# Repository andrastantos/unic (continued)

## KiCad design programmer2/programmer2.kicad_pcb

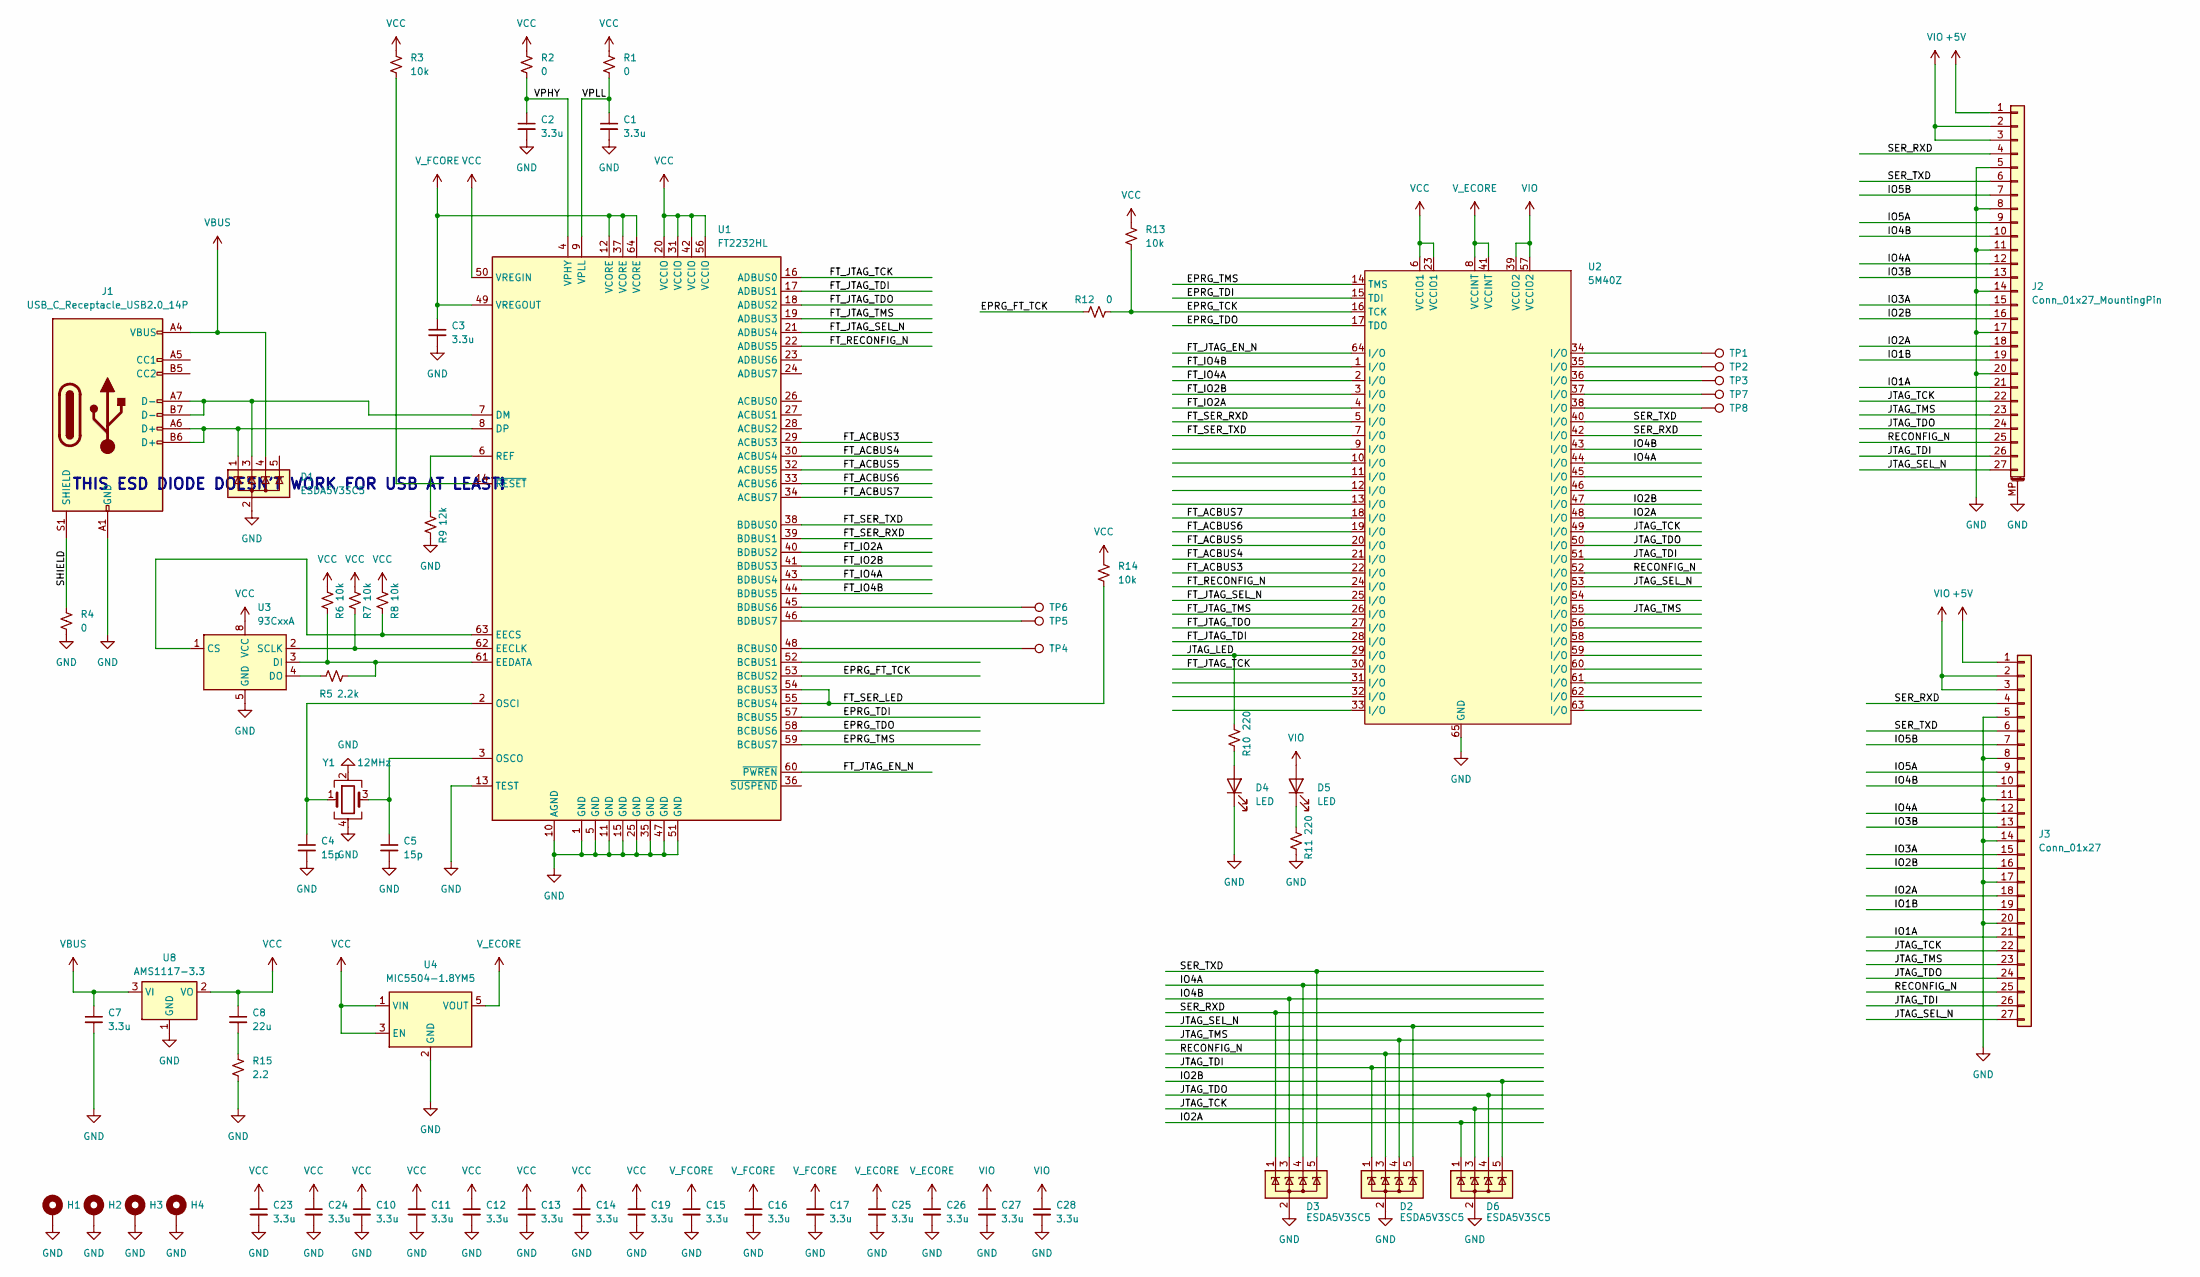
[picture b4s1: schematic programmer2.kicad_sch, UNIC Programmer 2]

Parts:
C1, C2, C3, C7, C10, C11, C12, C13, C14, C15, C16, C17, C19, C23, C24, C25, C26, C27, C28: 3.3u; C_0603_1608Metric_Pad1.08x0.95mm_HandSolder
C4, C5: 15p; C_0603_1608Metric_Pad1.08x0.95mm_HandSolder
C8: 22u; C_0805_2012Metric_Pad1.18x1.45mm_HandSolder
D1, D2, D3, D6: ESDA5V3SC5; SOT-23-5
D4, D5: LED; LED_0603_1608Metric_Pad1.05x0.95mm_HandSolder
H1, H2, H3, H4: MountingHole; MountingHole_3.2mm_M3_DIN965_Pad
J1: USB_C_Receptacle_USB2.0_14P; USB_C_Receptacle_HRO_TYPE-C-31-M-12; mpn 44116B01231
J2: Conn_01x27_MountingPin; Molex_502598-2793_2Rows-23P~0.60mm_Horizontal; mpn 502598-2793
J3: Conn_01x27; PinHeader_2x14_P2.54mm_Vertical
R1, R2, R4, R12: 0; R_0603_1608Metric_Pad0.98x0.95mm_HandSolder
R3, R6, R7, R8, R13, R14: 10k; R_0603_1608Metric_Pad0.98x0.95mm_HandSolder
R5: 2.2k; R_0603_1608Metric_Pad0.98x0.95mm_HandSolder
R9: 12k; R_0603_1608Metric_Pad0.98x0.95mm_HandSolder
R10, R11: 220; R_0603_1608Metric_Pad0.98x0.95mm_HandSolder
R15: 2.2; R_0603_1608Metric_Pad0.98x0.95mm_HandSolder
TP1, TP2, TP3, TP4, TP5, TP6, TP7, TP8: TestPoint; TestPoint_THTPad_1.0x1.0mm_Drill0.5mm
U1: FT2232HL; LQFP-64_10x10mm_P0.5mm
U2: 5M40Z; TQFP-64-1EP_10x10mm_P0.5mm_EP8x8mm
U3: 93CxxA; SO-8_3.9x4.9mm_P1.27mm
U4: MIC5504-1.8YM5; SOT-23-5
U8: AMS1117-3.3; SOT-223-3_TabPin2
Y1: 12MHz; Oscillator_SMD_Abracon_ASE-4Pin_3.2x2.5mm; mpn RH100-13.560-10-1020-EXT-TR

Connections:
+5V: J2.1, J3.1
/EPRG_FT_TCK: R12.1, U1.53 (BCBUS2)
/EPRG_TCK: R12.2, R13.2, U2.16 (TCK)
/EPRG_TDI: U1.57 (BCBUS5), U2.15 (TDI)
/EPRG_TDO: U1.58 (BCBUS6), U2.17 (TDO)
/EPRG_TMS: U1.59 (BCBUS7), U2.14 (TMS)
/FT_ACBUS3: U1.29 (ACBUS3), U2.22 (I/O)
/FT_ACBUS4: U1.30 (ACBUS4), U2.21 (I/O)
/FT_ACBUS5: U1.32 (ACBUS5), U2.20 (I/O)
/FT_ACBUS6: U1.33 (ACBUS6), U2.19 (I/O)
/FT_ACBUS7: U1.34 (ACBUS7), U2.18 (I/O)
/FT_IO2A: U1.40 (BDBUS2), U2.4 (I/O)
/FT_IO2B: U1.41 (BDBUS3), U2.3 (I/O)
/FT_IO4A: U1.43 (BDBUS4), U2.2 (I/O)
/FT_IO4B: U1.44 (BDBUS5), U2.1 (I/O)
/FT_JTAG_EN_N: U1.60 (~PWREN), U2.64 (I/O)
/FT_JTAG_SEL_N: U1.21 (ADBUS4), U2.25 (I/O)
/FT_JTAG_TCK: U1.16 (ADBUS0), U2.30 (I/O)
/FT_JTAG_TDI: U1.17 (ADBUS1), U2.28 (I/O)
/FT_JTAG_TDO: U1.18 (ADBUS2), U2.27 (I/O)
/FT_JTAG_TMS: U1.19 (ADBUS3), U2.26 (I/O)
/FT_RECONFIG_N: U1.22 (ADBUS5), U2.24 (I/O)
/FT_SER_LED: R14.2, U1.54 (BCBUS3), U1.55 (BCBUS4)
/FT_SER_RXD: U1.39 (BDBUS1), U2.5 (I/O)
/FT_SER_TXD: U1.38 (BDBUS0), U2.7 (I/O)
/IO1A: J2.21, J3.21
/IO1B: J2.19, J3.19
/IO2A: D6.1 (K), J2.18, J3.18, U2.48 (I/O)
/IO2B: D6.5 (K), J2.16, J3.16, U2.47 (I/O)
/IO3A: J2.15, J3.15
/IO3B: J2.13, J3.13
/IO4A: D3.4 (K), J2.12, J3.12, U2.44 (I/O)
/IO4B: D3.3 (K), J2.10, J3.10, U2.43 (I/O)
/IO5A: J2.9, J3.9
/IO5B: J2.7, J3.7
/JTAG_LED: R10.1, U2.29 (I/O)
/JTAG_SEL_N: D2.5 (K), J2.27, J3.27, U2.53 (I/O)
/JTAG_TCK: D6.3 (K), J2.22, J3.22, U2.49 (I/O)
/JTAG_TDI: D2.1 (K), J2.26, J3.26, U2.51 (I/O)
/JTAG_TDO: D6.4 (K), J2.24, J3.24, U2.50 (I/O)
/JTAG_TMS: D2.4 (K), J2.23, J3.23, U2.55 (I/O)
/RECONFIG_N: D2.3 (K), J2.25, J3.25, U2.52 (I/O)
/SER_RXD: D3.1 (K), J2.4, J3.4, U2.42 (I/O)
/SER_TXD: D3.5 (K), J2.6, J3.6, U2.40 (I/O)
/SHIELD: J1.S1 (SHIELD), R4.1
/VPHY: C2.1, R2.2, U1.4 (VPHY)
/VPLL: C1.1, R1.2, U1.9 (VPLL)
GND: C1.2, C2.2, C3.2, C4.2, C5.2, C7.2, C10.2, C11.2, C12.2, C13.2, C14.2, C15.2, C16.2, C17.2, C19.2, C23.2, C24.2, C25.2, C26.2, C27.2, C28.2, D1.2 (A), D2.2 (A), D3.2 (A), D4.1 (K), D6.2 (A), H1.1, H2.1, H3.1, H4.1, J1.A1 (GND), J1.A12 (GND), J1.B1 (GND), J1.B12 (GND), J2.5, J2.8, J2.11, J2.14, J2.17, J2.20, J2.MP (MountPin), J3.5, J3.8, J3.11, J3.14, J3.17, J3.20, R4.2, R9.2, R11.2, R15.2, U1.1 (GND), U1.5 (GND), U1.10 (AGND), U1.11 (GND), U1.13 (TEST), U1.15 (GND), U1.25 (GND), U1.35 (GND), U1.47 (GND), U1.51 (GND), U2.65 (GND), U3.5 (GND), U4.2 (GND), U8.1 (GND), Y1.2, Y1.4
unnamed: C8.2, R15.1
unnamed: D4.2 (A), R10.2
unnamed: D5.1 (K), R11.1
unnamed: TP1.1, U2.34 (I/O)
unnamed: TP2.1, U2.35 (I/O)
unnamed: TP3.1, U2.36 (I/O)
unnamed: TP7.1, U2.37 (I/O)
unnamed: TP8.1, U2.38 (I/O)
unnamed: TP4.1, U1.48 (BCBUS0)
unnamed: TP6.1, U1.45 (BDBUS6)
unnamed: TP5.1, U1.46 (BDBUS7)
unnamed: D1.3 (K), J1.A7 (D-), J1.B7 (D-), U1.7 (DM)
unnamed: D1.1 (K), J1.A6 (D+), J1.B6 (D+), U1.8 (DP)
unnamed: R7.2, U1.62 (EECLK), U3.2 (SCLK)
unnamed: R8.2, U1.63 (EECS), U3.1 (CS)
unnamed: R5.2, R6.2, U1.61 (EEDATA), U3.3 (DI)
unnamed: C4.1, U1.2 (OSCI), Y1.1
unnamed: C5.1, U1.3 (OSCO), Y1.3
unnamed: R9.1, U1.6 (REF)
unnamed: R3.2, U1.14 (~RESET)
unnamed: R5.1, U3.4 (DO)
VBUS: C7.1, D1.4 (K), J1.A4 (VBUS), J1.A9 (VBUS), J1.B4 (VBUS), J1.B9 (VBUS), U8.3 (VI)
VCC: C8.1, C10.1, C11.1, C12.1, C13.1, C14.1, C19.1, C23.1, C24.1, R1.1, R2.1, R3.1, R6.1, R7.1, R8.1, R13.1, R14.1, U1.20 (VCCIO), U1.31 (VCCIO), U1.42 (VCCIO), U1.50 (VREGIN), U1.56 (VCCIO), U2.6 (VCCIO1), U2.23 (VCCIO1), U3.8 (VCC), U4.1 (VIN), U4.3 (EN), U8.2 (VO)
VIO: C27.1, C28.1, D5.2 (A), J2.2, J2.3, J3.2, J3.3, U2.39 (VCCIO2), U2.57 (VCCIO2)
V_ECORE: C25.1, C26.1, U2.8 (VCCINT), U2.41 (VCCINT), U4.5 (VOUT)
V_FCORE: C3.1, C15.1, C16.1, C17.1, U1.12 (VCORE), U1.37 (VCORE), U1.49 (VREGOUT), U1.64 (VCORE)

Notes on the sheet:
THIS ESD DIODE DOESN'T WORK FOR USB AT LEAST!

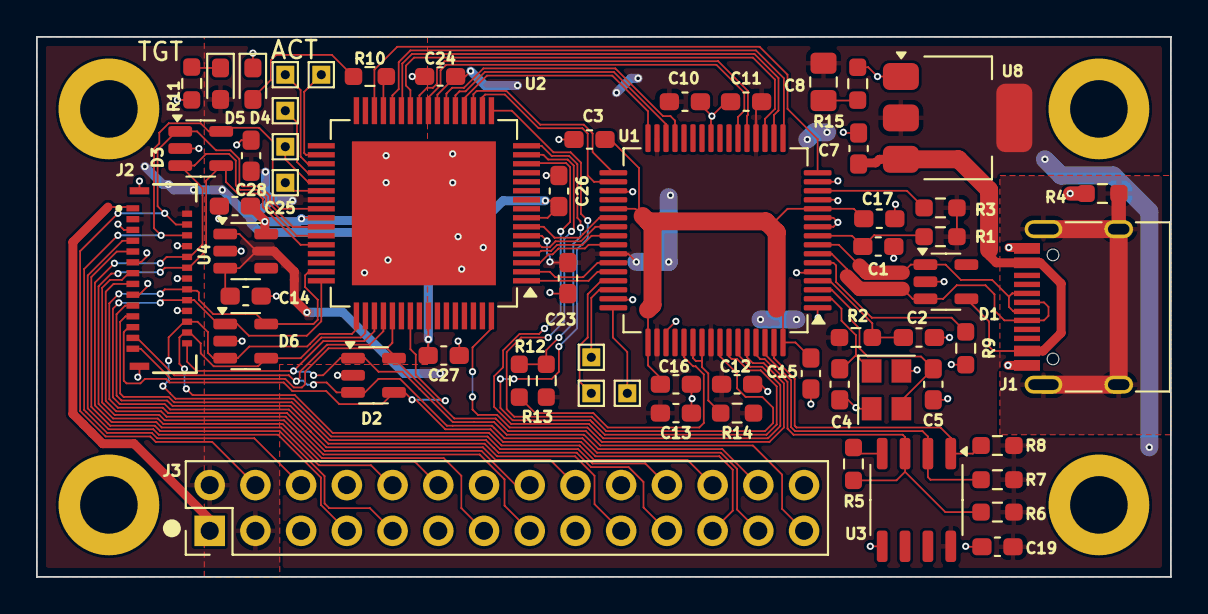
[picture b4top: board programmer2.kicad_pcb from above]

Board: 2 copper layers, 63.0 x 30.0 mm, 64 parts (0 on the bottom side), 74 nets.

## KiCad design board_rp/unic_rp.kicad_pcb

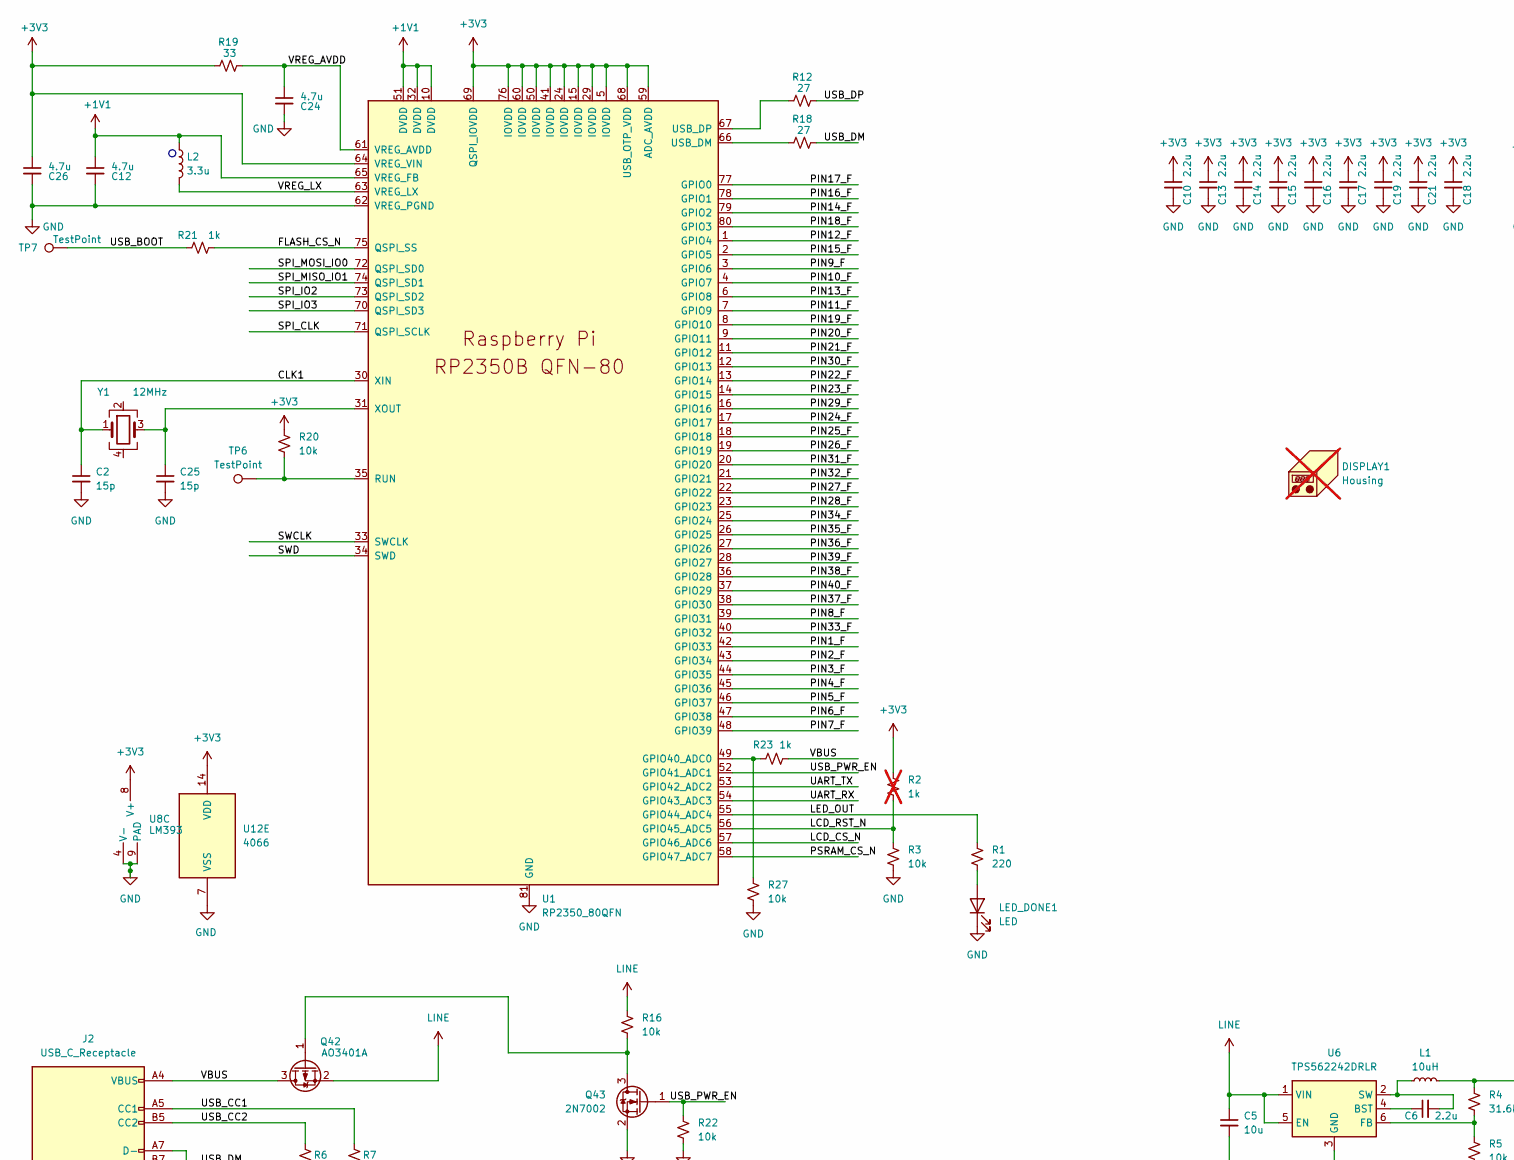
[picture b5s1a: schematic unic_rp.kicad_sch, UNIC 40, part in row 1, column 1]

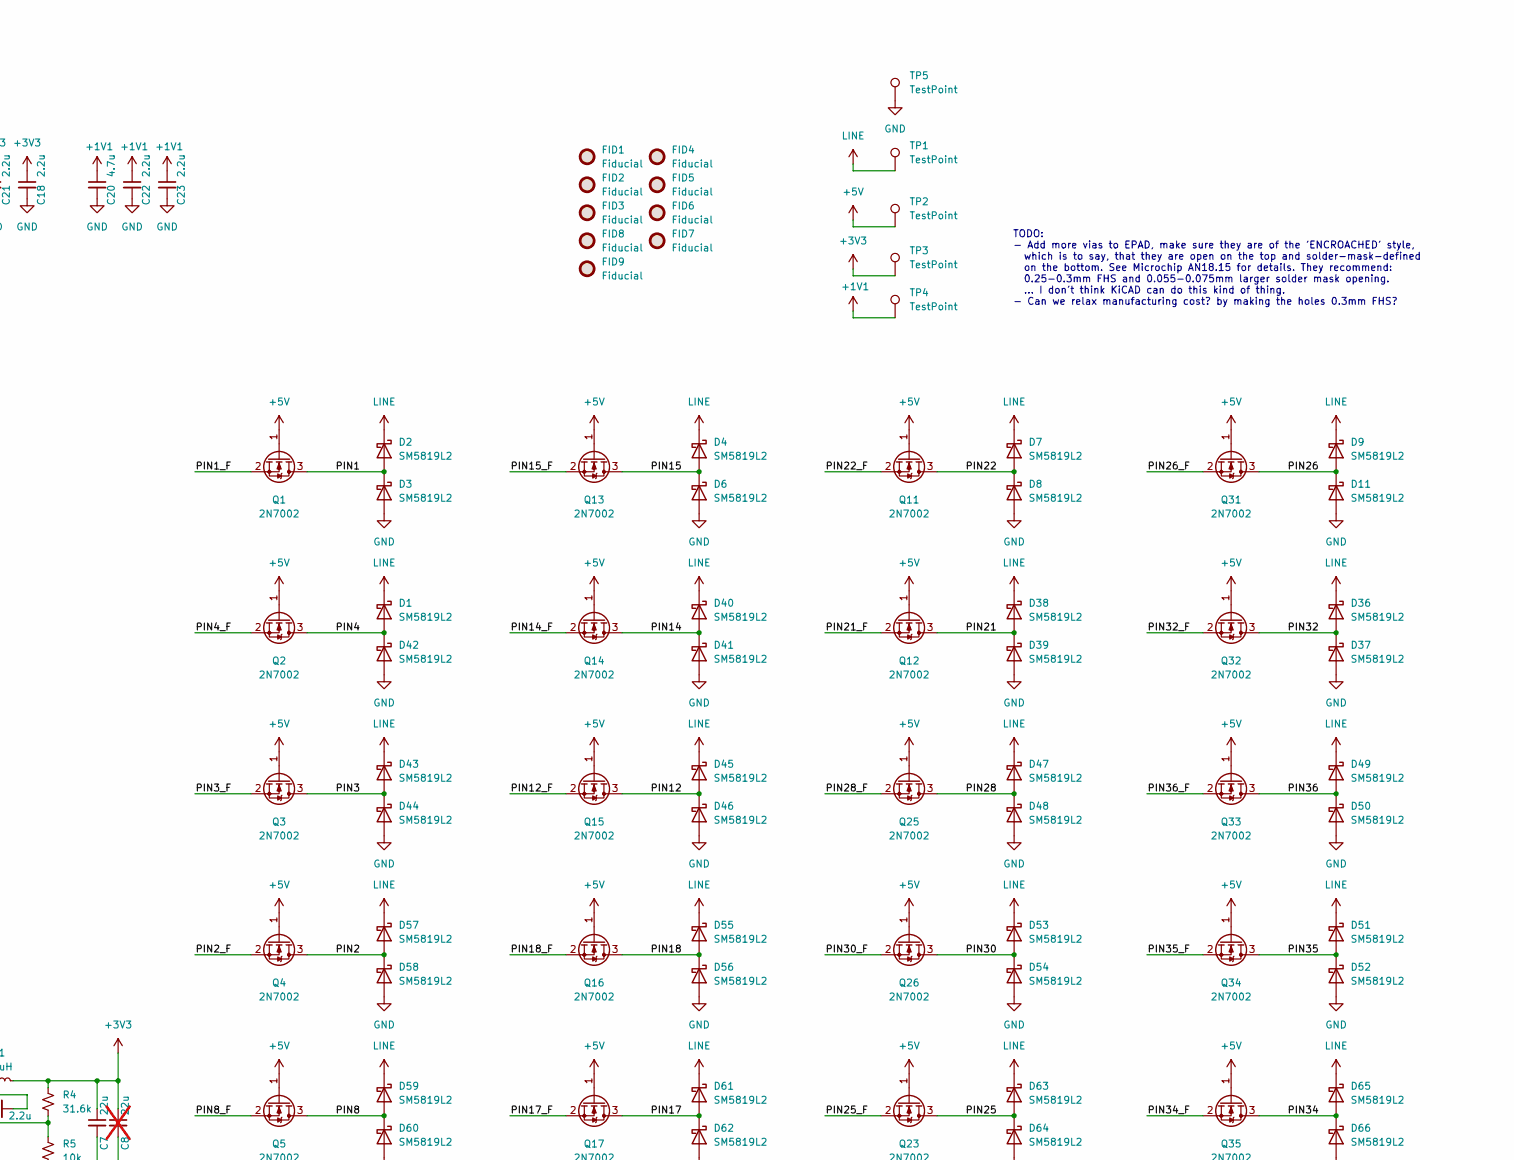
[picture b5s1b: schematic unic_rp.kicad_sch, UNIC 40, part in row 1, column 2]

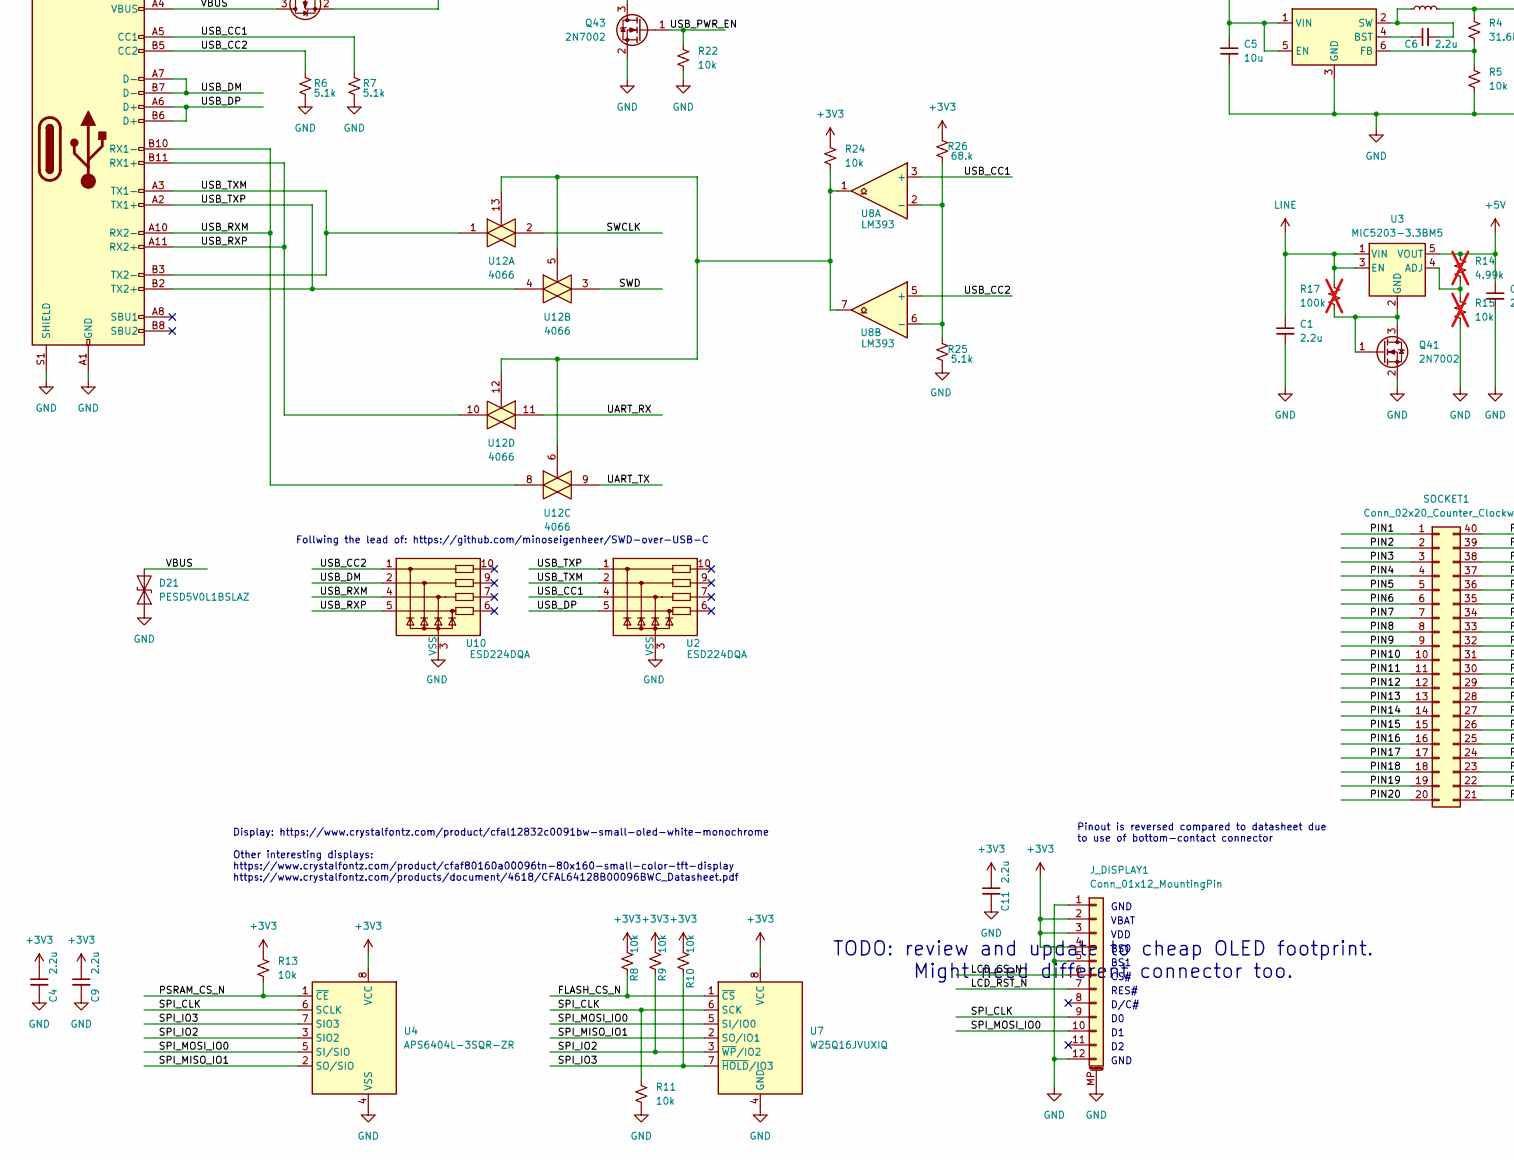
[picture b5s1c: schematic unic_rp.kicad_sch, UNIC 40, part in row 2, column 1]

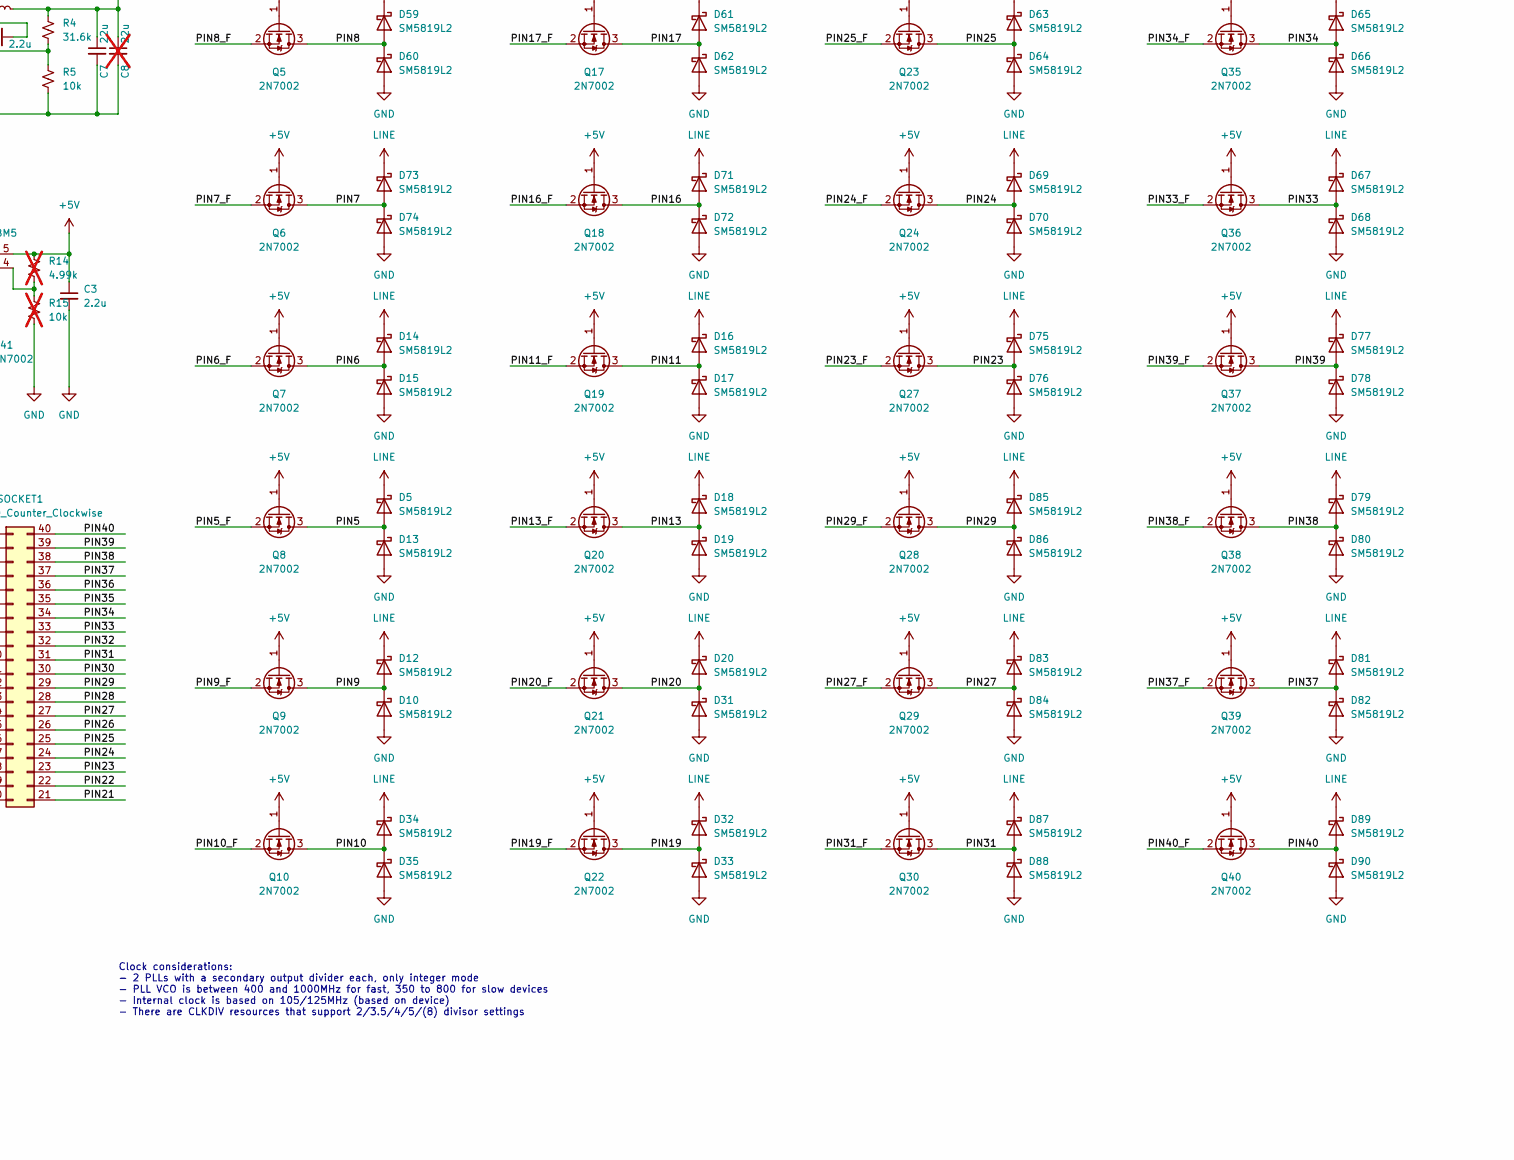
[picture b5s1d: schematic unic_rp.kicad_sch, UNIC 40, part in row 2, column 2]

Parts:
C1, C3, C4, C6, C9, C10, C11, C13, C14, C15, C16, C17, C18, C19, C21, C22, C23: 2.2u; C_0402_1005Metric_Pad0.74x0.62mm_HandSolder; mpn CC0402MRX5R6BB225
C2, C25: 15p; C_0402_1005Metric_Pad0.74x0.62mm_HandSolder
C5: 10u; C_0805_2012Metric_Pad1.18x1.45mm_HandSolder; mpn CL21A106KAYNNNG
C7: 22u; C_0805_2012Metric_Pad1.18x1.45mm_HandSolder; mpn CL21A226MQQNNNE
C8: 22u; C_0805_2012Metric_Pad1.18x1.45mm_HandSolder; mpn CL21A226MQQNNNE; not fitted
C12, C20, C24, C26: 4.7u; C_0402_1005Metric_Pad0.74x0.62mm_HandSolder
D1, D2, D3, D4, D5, D6, D7, D8, D9, D10, D11, D12, D13, D14, D15, D16, D17, D18, D19, D20, D31, D32, D33, D34, D35, D36, D37, D38, D39, D40, D41, D42, D43, D44, D45, D46, D47, D48, D49, D50, D51, D52, D53, D54, D55, D56, D57, D58, D59, D60, D61, D62, D63, D64, D65, D66, D67, D68, D69, D70, D71, D72, D73, D74, D75, D76, D77, D78, D79, D80, D81, D82, D83, D84, D85, D86, D87, D88, D89, D90: SM5819L2; D_SOD-882
D21: PESD5V0L1BSLAZ; D_SOD-882
DISPLAY1: Housing; CFAL12832C-0091B-W_A; mpn CFAL12832C-0091B-W_A; not fitted
FID1, FID2, FID3, FID4, FID5, FID6, FID7, FID8, FID9: Fiducial; Fiducial_0.5mm_Mask1mm
J2: USB_C_Receptacle; USB_C_Receptacle_GCT_USB4115-03-C
J_DISPLAY1: Conn_01x12_MountingPin; CF31121D0R0-05-NH; mpn CF31121D0R0-05-NH
L1: 10uH; L_1008_2520Metric_Pad1.43x2.20mm_HandSolder; mpn UHP 252012BF-100M
L2: 3.3u; L_Cenker_CKCS201610; mpn WIP201610S-4R7MLDG
LED_DONE1: LED; LED_0402_1005Metric_Pad0.77x0.64mm_HandSolder; mpn CS42C-QL4
Q1, Q2, Q3, Q4, Q5, Q6, Q7, Q8, Q9, Q10, Q11, Q12, Q13, Q14, Q15, Q16, Q17, Q18, Q19, Q20, Q21, Q22, Q23, Q24, Q25, Q26, Q27, Q28, Q29, Q30, Q31, Q32, Q33, Q34, Q35, Q36, Q37, Q38, Q39, Q40, Q41, Q43: 2N7002; SOT-883; mpn 2N7002KL3A-TP
Q42: AO3401A; SOT-23
R1: 220; R_0402_1005Metric_Pad0.72x0.64mm_HandSolder; mpn CR0402-JW-221GLF
R2: 1k; R_0402_1005Metric_Pad0.72x0.64mm_HandSolder; mpn CR0402-JW-102GLF; not fitted
R3, R5, R8, R9, R10, R11, R13, R16, R20, R22, R24, R27: 10k; R_0402_1005Metric_Pad0.72x0.64mm_HandSolder; mpn CR0402-FX-1002GLF
R4: 31.6k; R_0402_1005Metric_Pad0.72x0.64mm_HandSolder; mpn CR0402-FX-3162GLF
R6, R7, R25: 5.1k; R_0402_1005Metric_Pad0.72x0.64mm_HandSolder
R12, R18: 27; R_0402_1005Metric_Pad0.72x0.64mm_HandSolder
R14: 4.99k; R_0402_1005Metric_Pad0.72x0.64mm_HandSolder; mpn CR0402-FX-4991GLF; not fitted
R15: 10k; R_0402_1005Metric_Pad0.72x0.64mm_HandSolder; mpn CR0402-FX-1002GLF; not fitted
R17: 100k; R_0402_1005Metric_Pad0.72x0.64mm_HandSolder; mpn CR0402-FX-1002GLF; not fitted
R19: 33; R_0402_1005Metric_Pad0.72x0.64mm_HandSolder
R21: 1k; R_0402_1005Metric_Pad0.72x0.64mm_HandSolder
R23: 1k; R_0402_1005Metric_Pad0.72x0.64mm_HandSolder; mpn CR0402-JW-102GLF
R26: 68.k; R_0402_1005Metric_Pad0.72x0.64mm_HandSolder
SOCKET1: Conn_02x20_Counter_Clockwise; DIP-40_pin_header; mpn BA3760-TUBL-4A-F5
TP1, TP2, TP3, TP4, TP5, TP6, TP7: TestPoint; TestPoint_Pad_D2.0mm
U1: RP2350_80QFN; RP2350-QFN-80-1EP_10x10_P0.4mm_EP3.4x3.4mm
U2, U10: ESD224DQA; Diodes_UDFN-10_1.0x2.5mm_P0.5mm; mpn TVU1240R1ADG
U3: MIC5203-3.3BM5; SOT-23-5; mpn MIC5203-3.3YM5-TR
U4: APS6404L-3SQR-ZR; W25Q16JVUXIQ_TR; mpn APS6404L-3SQR-ZR
U6: TPS562242DRLR; SOT-563; mpn AP62150Z6-7
U7: W25Q16JVUXIQ; W25Q16JVUXIQ_TR; mpn W25Q16JVUXIQ TR
U8: LM393; WSON-8-1EP_2x2mm_P0.5mm_EP0.9x1.6mm; mpn LM393BIDSGR
U12: 4066; DHVQFN-14-1EP_2.5x3mm_P0.5mm_EP1x1.5mm; mpn 74HC4066BQ,115
Y1: 12MHz; Oscillator_SMD_Abracon_ASE-4Pin_3.2x2.5mm; mpn RH100-13.560-10-1020-EXT-TR

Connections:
+1V1: C12.1, C20.1, C22.1, C23.1, L2.1, TP4.1, U1.10 (DVDD), U1.32 (DVDD), U1.51 (DVDD), U1.65 (VREG_FB)
+3V3: C4.1, C7.1, C8.1, C9.1, C10.1, C11.1, C13.1, C14.1, C15.1, C16.1, C17.1, C18.1, C19.1, C21.1, C26.1, J_DISPLAY1.2, J_DISPLAY1.3, J_DISPLAY1.4, L1.2, R2.1, R4.1, R8.1, R9.1, R10.1, R13.1, R19.1, R20.1, R24.1, R26.2, TP3.1, U1.5 (IOVDD), U1.15 (IOVDD), U1.24 (IOVDD), U1.29 (IOVDD), U1.41 (IOVDD), U1.50 (IOVDD), U1.59 (ADC_AVDD), U1.60 (IOVDD), U1.64 (VREG_VIN), U1.68 (USB_OTP_VDD), U1.69 (QSPI_IOVDD), U1.76 (IOVDD), U4.8 (VCC), U7.8 (VCC), U8.8 (V+), U12.14 (VDD)
+5V: C3.1, Q1.1 (G), Q2.1 (G), Q3.1 (G), Q4.1 (G), Q5.1 (G), Q6.1 (G), Q7.1 (G), Q8.1 (G), Q9.1 (G), Q10.1 (G), Q11.1 (G), Q12.1 (G), Q13.1 (G), Q14.1 (G), Q15.1 (G), Q16.1 (G), Q17.1 (G), Q18.1 (G), Q19.1 (G), Q20.1 (G), Q21.1 (G), Q22.1 (G), Q23.1 (G), Q24.1 (G), Q25.1 (G), Q26.1 (G), Q27.1 (G), Q28.1 (G), Q29.1 (G), Q30.1 (G), Q31.1 (G), Q32.1 (G), Q33.1 (G), Q34.1 (G), Q35.1 (G), Q36.1 (G), Q37.1 (G), Q38.1 (G), Q39.1 (G), Q40.1 (G), R14.1, TP2.1, U3.5 (VOUT)
/CLK1: C2.1, U1.30 (XIN), Y1.1
/FLASH_CS_N: R8.2, R21.2, U1.75 (QSPI_SS), U7.1 (~CS)
/LCD_CS_N: J_DISPLAY1.6, U1.57 (GPIO46_ADC6)
/LCD_RST_N: J_DISPLAY1.7, R2.2, R3.1, U1.56 (GPIO45_ADC5)
/LED_OUT: R1.1, U1.55 (GPIO44_ADC4)
/PIN1: D2.2 (A), D3.1 (K), Q1.3 (D), SOCKET1.1
/PIN1_F: Q1.2 (S), U1.42 (GPIO33)
/PIN2: D57.2 (A), D58.1 (K), Q4.3 (D), SOCKET1.2
/PIN2_F: Q4.2 (S), U1.43 (GPIO34)
/PIN3: D43.2 (A), D44.1 (K), Q3.3 (D), SOCKET1.3
/PIN3_F: Q3.2 (S), U1.44 (GPIO35)
/PIN4: D1.2 (A), D42.1 (K), Q2.3 (D), SOCKET1.4
/PIN4_F: Q2.2 (S), U1.45 (GPIO36)
/PIN5: D5.2 (A), D13.1 (K), Q8.3 (D), SOCKET1.5
/PIN5_F: Q8.2 (S), U1.46 (GPIO37)
/PIN6: D14.2 (A), D15.1 (K), Q7.3 (D), SOCKET1.6
/PIN6_F: Q7.2 (S), U1.47 (GPIO38)
/PIN7: D73.2 (A), D74.1 (K), Q6.3 (D), SOCKET1.7
/PIN7_F: Q6.2 (S), U1.48 (GPIO39)
/PIN8: D59.2 (A), D60.1 (K), Q5.3 (D), SOCKET1.8
/PIN8_F: Q5.2 (S), U1.39 (GPIO31)
/PIN9: D10.1 (K), D12.2 (A), Q9.3 (D), SOCKET1.9
/PIN9_F: Q9.2 (S), U1.3 (GPIO6)
/PIN10: D34.2 (A), D35.1 (K), Q10.3 (D), SOCKET1.10
/PIN10_F: Q10.2 (S), U1.4 (GPIO7)
/PIN11: D16.2 (A), D17.1 (K), Q19.3 (D), SOCKET1.11
/PIN11_F: Q19.2 (S), U1.7 (GPIO9)
/PIN12: D45.2 (A), D46.1 (K), Q15.3 (D), SOCKET1.12
/PIN12_F: Q15.2 (S), U1.1 (GPIO4)
/PIN13: D18.2 (A), D19.1 (K), Q20.3 (D), SOCKET1.13
/PIN13_F: Q20.2 (S), U1.6 (GPIO8)
/PIN14: D40.2 (A), D41.1 (K), Q14.3 (D), SOCKET1.14
/PIN14_F: Q14.2 (S), U1.79 (GPIO2)
/PIN15: D4.2 (A), D6.1 (K), Q13.3 (D), SOCKET1.15
/PIN15_F: Q13.2 (S), U1.2 (GPIO5)
/PIN16: D71.2 (A), D72.1 (K), Q18.3 (D), SOCKET1.16
/PIN16_F: Q18.2 (S), U1.78 (GPIO1)
/PIN17: D61.2 (A), D62.1 (K), Q17.3 (D), SOCKET1.17
/PIN17_F: Q17.2 (S), U1.77 (GPIO0)
/PIN18: D55.2 (A), D56.1 (K), Q16.3 (D), SOCKET1.18
/PIN18_F: Q16.2 (S), U1.80 (GPIO3)
/PIN19: D32.2 (A), D33.1 (K), Q22.3 (D), SOCKET1.19
/PIN19_F: Q22.2 (S), U1.8 (GPIO10)
/PIN20: D20.2 (A), D31.1 (K), Q21.3 (D), SOCKET1.20
/PIN20_F: Q21.2 (S), U1.9 (GPIO11)
/PIN21: D38.2 (A), D39.1 (K), Q12.3 (D), SOCKET1.21
/PIN21_F: Q12.2 (S), U1.11 (GPIO12)
/PIN22: D7.2 (A), D8.1 (K), Q11.3 (D), SOCKET1.22
/PIN22_F: Q11.2 (S), U1.13 (GPIO14)
/PIN23: D75.2 (A), D76.1 (K), Q27.3 (D), SOCKET1.23
/PIN23_F: Q27.2 (S), U1.14 (GPIO15)
/PIN24: D69.2 (A), D70.1 (K), Q24.3 (D), SOCKET1.24
/PIN24_F: Q24.2 (S), U1.17 (GPIO17)
/PIN25: D63.2 (A), D64.1 (K), Q23.3 (D), SOCKET1.25
/PIN25_F: Q23.2 (S), U1.18 (GPIO18)
/PIN26: D9.2 (A), D11.1 (K), Q31.3 (D), SOCKET1.26
/PIN26_F: Q31.2 (S), U1.19 (GPIO19)
/PIN27: D83.2 (A), D84.1 (K), Q29.3 (D), SOCKET1.27
/PIN27_F: Q29.2 (S), U1.22 (GPIO22)
/PIN28: D47.2 (A), D48.1 (K), Q25.3 (D), SOCKET1.28
/PIN28_F: Q25.2 (S), U1.23 (GPIO23)
/PIN29: D85.2 (A), D86.1 (K), Q28.3 (D), SOCKET1.29
/PIN29_F: Q28.2 (S), U1.16 (GPIO16)
/PIN30: D53.2 (A), D54.1 (K), Q26.3 (D), SOCKET1.30
/PIN30_F: Q26.2 (S), U1.12 (GPIO13)
/PIN31: D87.2 (A), D88.1 (K), Q30.3 (D), SOCKET1.31
/PIN31_F: Q30.2 (S), U1.20 (GPIO20)
/PIN32: D36.2 (A), D37.1 (K), Q32.3 (D), SOCKET1.32
/PIN32_F: Q32.2 (S), U1.21 (GPIO21)
/PIN33: D67.2 (A), D68.1 (K), Q36.3 (D), SOCKET1.33
/PIN33_F: Q36.2 (S), U1.40 (GPIO32)
/PIN34: D65.2 (A), D66.1 (K), Q35.3 (D), SOCKET1.34
/PIN34_F: Q35.2 (S), U1.25 (GPIO24)
/PIN35: D51.2 (A), D52.1 (K), Q34.3 (D), SOCKET1.35
/PIN35_F: Q34.2 (S), U1.26 (GPIO25)
/PIN36: D49.2 (A), D50.1 (K), Q33.3 (D), SOCKET1.36
/PIN36_F: Q33.2 (S), U1.27 (GPIO26)
/PIN37: D81.2 (A), D82.1 (K), Q39.3 (D), SOCKET1.37
/PIN37_F: Q39.2 (S), U1.38 (GPIO30)
/PIN38: D79.2 (A), D80.1 (K), Q38.3 (D), SOCKET1.38
/PIN38_F: Q38.2 (S), U1.36 (GPIO28)
/PIN39: D77.2 (A), D78.1 (K), Q37.3 (D), SOCKET1.39
/PIN39_F: Q37.2 (S), U1.28 (GPIO27)
/PIN40: D89.2 (A), D90.1 (K), Q40.3 (D), SOCKET1.40
/PIN40_F: Q40.2 (S), U1.37 (GPIO29)
/PSRAM_CS_N: R13.2, U1.58 (GPIO47_ADC7), U4.1 (~CE)
/SPI_CLK: J_DISPLAY1.9, R11.1, U1.71 (QSPI_SCLK), U4.6 (SCLK), U7.6 (SCK)
/SPI_IO2: R9.2, U1.73 (QSPI_SD2), U4.3 (SIO2), U7.3 (~WP/IO2)
/SPI_IO3: R10.2, U1.70 (QSPI_SD3), U4.7 (SIO3), U7.7 (~HOLD/IO3)
/SPI_MISO_IO1: U1.74 (QSPI_SD1), U4.2 (SO/SIO), U7.2 (SO/IO1)
/SPI_MOSI_IO0: J_DISPLAY1.10, U1.72 (QSPI_SD0), U4.5 (SI/SIO), U7.5 (SI/IO0)
/SWCLK: U1.33 (SWCLK), U12.2
/SWD: U1.34 (SWD), U12.3
/UART_RX: U1.54 (GPIO43_ADC3), U12.11
/UART_TX: U1.53 (GPIO42_ADC2), U12.9
/USB_BOOT: R21.1, TP7.1
/USB_CC1: J2.A5 (CC1), R7.2, U2.4, U8.3 (+)
/USB_CC2: J2.B5 (CC2), R6.2, U8.5 (+), U10.1
/USB_DM: J2.A7 (D-), J2.B7 (D-), R18.2, U10.2
/USB_DP: J2.A6 (D+), J2.B6 (D+), R12.2, U2.5
/USB_PWR_EN: Q43.1 (G), R22.1, U1.52 (GPIO41_ADC1)
/USB_RXM: J2.A10 (RX2-), J2.B10 (RX1-), U10.4, U12.8
/USB_RXP: J2.A11 (RX2+), J2.B11 (RX1+), U10.5, U12.10
/USB_TXM: J2.A3 (TX1-), J2.B3 (TX2-), U2.2, U12.1
/USB_TXP: J2.A2 (TX1+), J2.B2 (TX2+), U2.1, U12.4
/VBUS: D21.2 (A2), J2.A4 (VBUS), J2.A9 (VBUS), J2.B4 (VBUS), J2.B9 (VBUS), Q42.3 (D), R23.2
/VREG_AVDD: C24.1, R19.2, U1.61 (VREG_AVDD)
/VREG_LX: L2.2, U1.63 (VREG_LX)
GND: C1.2, C2.2, C3.2, C4.2, C5.2, C7.2, C8.2, C9.2, C10.2, C11.2, C12.2, C13.2, C14.2, C15.2, C16.2, C17.2, C18.2, C19.2, C20.2, C21.2, C22.2, C23.2, C24.2, C25.2, C26.2, D3.2 (A), D6.2 (A), D8.2 (A), D10.2 (A), D11.2 (A), D13.2 (A), D15.2 (A), D17.2 (A), D19.2 (A), D21.1 (A1), D31.2 (A), D33.2 (A), D35.2 (A), D37.2 (A), D39.2 (A), D41.2 (A), D42.2 (A), D44.2 (A), D46.2 (A), D48.2 (A), D50.2 (A), D52.2 (A), D54.2 (A), D56.2 (A), D58.2 (A), D60.2 (A), D62.2 (A), D64.2 (A), D66.2 (A), D68.2 (A), D70.2 (A), D72.2 (A), D74.2 (A), D76.2 (A), D78.2 (A), D80.2 (A), D82.2 (A), D84.2 (A), D86.2 (A), D88.2 (A), D90.2 (A), J2.A1 (GND), J2.A12 (GND), J2.B1 (GND), J2.B12 (GND), J2.S1 (SHIELD), J_DISPLAY1.1, J_DISPLAY1.5, J_DISPLAY1.12, J_DISPLAY1.MP (MountPin), LED_DONE1.1 (K), Q41.2 (S), Q43.2 (S), R3.2, R5.2, R6.1, R7.1, R11.2, R15.2, R22.2, R25.1, R27.2, TP5.1, U1.62 (VREG_PGND), U1.81 (GND), U2.3 (VSS), U2.8 (VSS), U4.4 (VSS), U6.3 (GND), U7.4 (GND), U8.4 (V-), U8.9 (PAD), U10.3 (VSS), U10.8 (VSS), U12.7 (VSS)
LINE: C1.1, C5.1, D1.1 (K), D2.1 (K), D4.1 (K), D5.1 (K), D7.1 (K), D9.1 (K), D12.1 (K), D14.1 (K), D16.1 (K), D18.1 (K), D20.1 (K), D32.1 (K), D34.1 (K), D36.1 (K), D38.1 (K), D40.1 (K), D43.1 (K), D45.1 (K), D47.1 (K), D49.1 (K), D51.1 (K), D53.1 (K), D55.1 (K), D57.1 (K), D59.1 (K), D61.1 (K), D63.1 (K), D65.1 (K), D67.1 (K), D69.1 (K), D71.1 (K), D73.1 (K), D75.1 (K), D77.1 (K), D79.1 (K), D81.1 (K), D83.1 (K), D85.1 (K), D87.1 (K), D89.1 (K), Q42.2 (S), R16.1, R17.1, TP1.1, U3.1 (VIN), U3.3 (EN), U6.1 (VIN), U6.5 (EN)
unnamed: LED_DONE1.2 (A), R1.2
unnamed: Q41.1 (G), Q41.3 (D), R17.2, U3.2 (GND)
unnamed: Q42.1 (G), Q43.3 (D), R16.2
unnamed: R24.2, U8.1, U8.7, U12.5, U12.6, U12.12, U12.13
unnamed: R23.1, R27.1, U1.49 (GPIO40_ADC0)
unnamed: R20.2, TP6.1, U1.35 (RUN)
unnamed: R18.1, U1.66 (USB_DM)
unnamed: R12.1, U1.67 (USB_DP)
unnamed: C25.1, U1.31 (XOUT), Y1.3
unnamed: R14.2, R15.1, U3.4 (ADJ)
unnamed: C6.1, U6.4 (BST)
unnamed: R4.2, R5.1, U6.6 (FB)
unnamed: C6.2, L1.1, U6.2 (SW)
unnamed: R25.2, R26.1, U8.2 (-), U8.6 (-)

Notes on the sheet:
Pinout is reversed compared to datasheet due to use of bottom-contact connector
CS#
Follwing the lead of: https://github.com/minoseigenheer/SWD-over-USB-C
TODO: - Add more vias to EPAD, make sure they are of the 'ENCROACHED' style, which is to say, that they are open on the top and solder-mask-defined on the bottom. See Microchip AN18.15 for details. They recommend: 0.25-0.3mm FHS and 0.055-0.075mm larger solder mask opening. ... I don't think KiCAD 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
GND
Clock considerations: - 2 PLLs with a secondary output divider each, only integer mode - PLL VCO is between 400 and 1000MHz for fast, 350 to 800 for slow devices - Internal clock is based on 105/125MHz (based on device) - There are CLKDIV resources that support 2/3.5/4/5/(8) divisor settings
VDD
RES#
BS1
TODO: review and update to cheap OLED footprint. Might need different connector too.
D/C#
Display: https://www.crystalfontz.com/product/cfal12832c0091bw-small-oled-white-monochrome Other interesting displays: https://www.crystalfontz.com/product/cfaf80160a00096tn-80x160-small-color-tft-display https://www.crystalfontz.com/products/document/4618/CFAL64128B00096BWC_Datasheet.pdf
BS0
VBAT

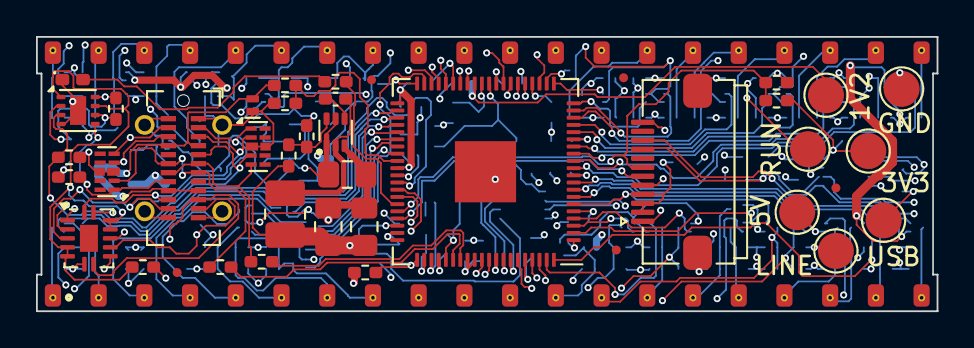
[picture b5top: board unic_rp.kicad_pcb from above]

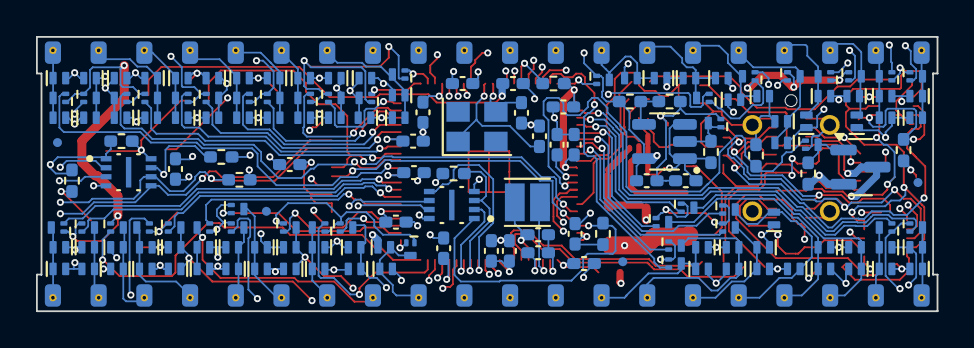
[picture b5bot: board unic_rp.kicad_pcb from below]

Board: 4 copper layers, 50.0 x 15.2 mm, 210 parts (167 on the bottom side), 127 nets.
